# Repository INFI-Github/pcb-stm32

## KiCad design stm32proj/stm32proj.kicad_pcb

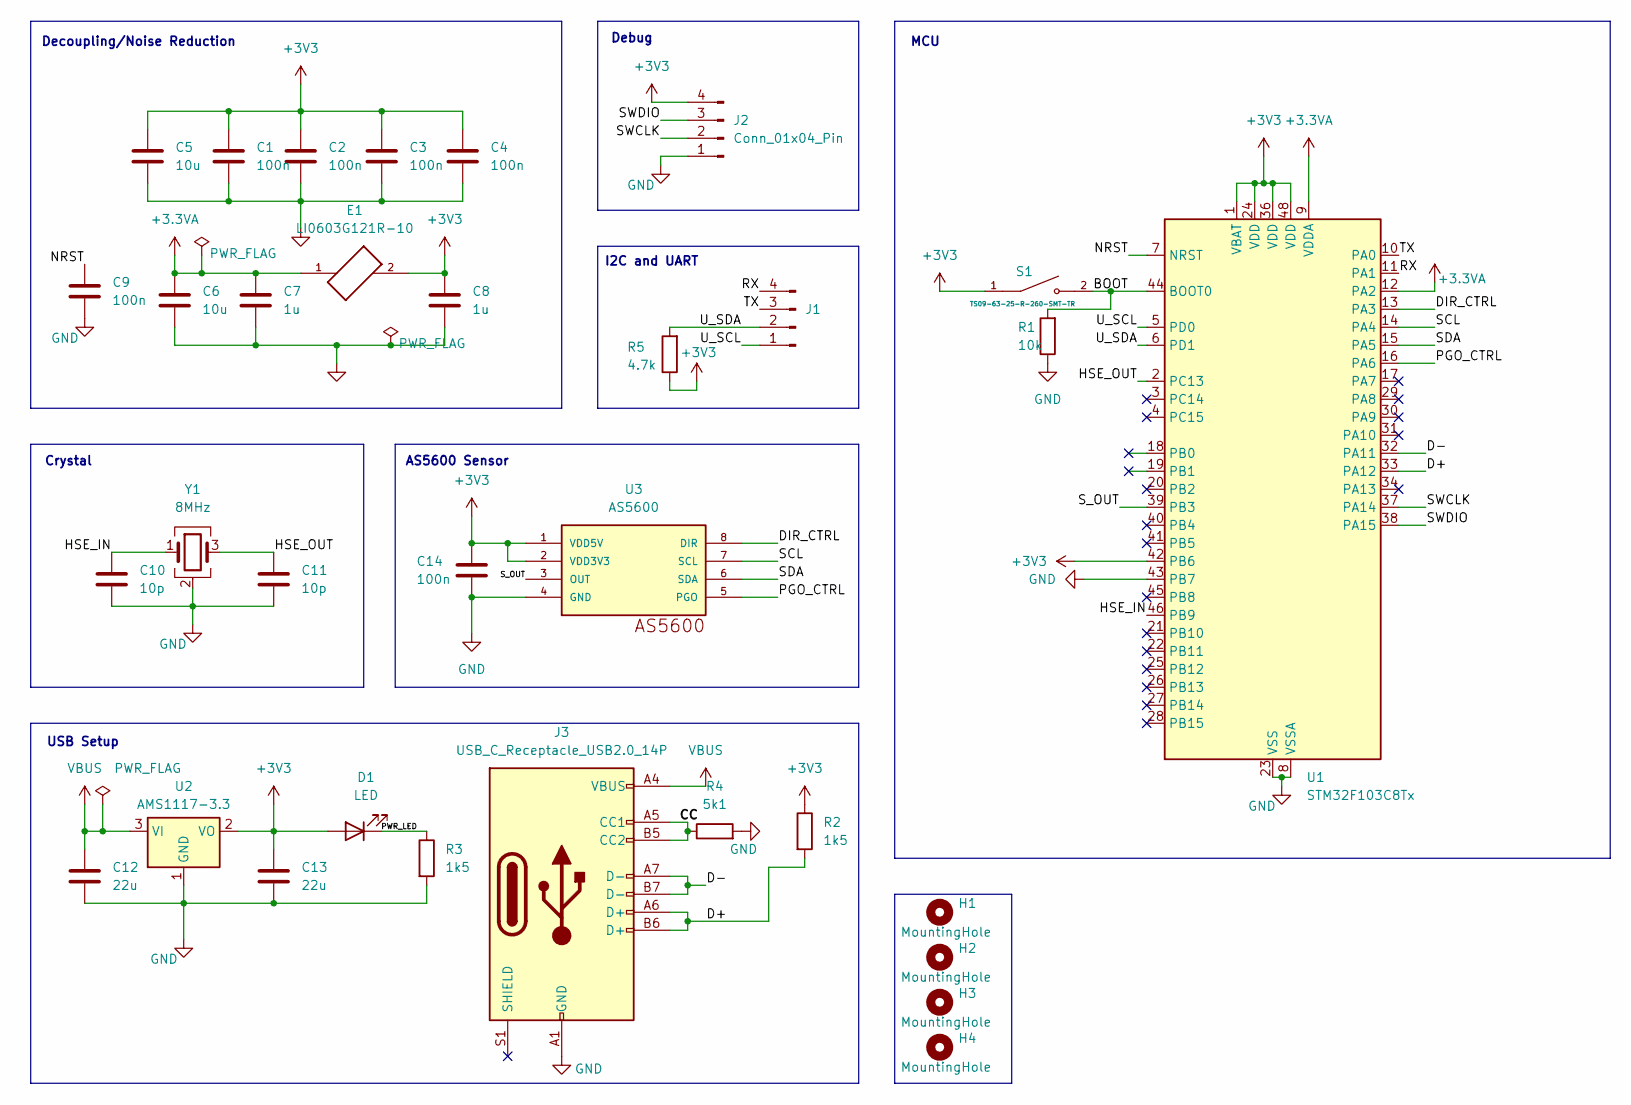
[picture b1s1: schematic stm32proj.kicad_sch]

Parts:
C1, C2, C3, C4, C9, C14: 100n; C_0402_1005Metric
C5, C6: 10u; C_0402_1005Metric
C7, C8: 1u; C_0402_1005Metric
C10, C11: 10p; C_0402_1005Metric
C12, C13: 22u; C_0805_2012Metric
D1: LED; LED_01005_0402Metric
E1: LI0603G121R-10; FB_LI0603G121R-10; PARTREV C
H1, H2, H3, H4: MountingHole; MountingHole_2.1mm
J1, J2: Conn_01x04_Pin; PinHeader_1x04_P1.00mm_Vertical
J3: USB_C_Receptacle_USB2.0_14P; USB_C_Receptacle_GCT_USB4105-xx-A_16P_TopMnt_Horizontal
R1: 10k; R_0402_1005Metric
R2, R3: 1k5; R_0402_1005Metric
R4: 5k1; R_0402_1005Metric
R5: 4.7k; R_0402_1005Metric
S1: TS09-63-25-R-260-SMT-TR; SW_TS09-63-25-R-260-SMT-TR; PARTREV 1.0
U1: STM32F103C8Tx; LQFP-48_7x7mm_P0.5mm
U2: AMS1117-3.3; SOT-223-3_TabPin2
U3: AS5600; SOIC8
Y1: 8MHz; Crystal_SMD_3225-4Pin_3.2x2.5mm

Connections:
+3.3VA: C6.1, C7.1, E1.1, U1.9 (VDDA), U1.12 (PA2)
+3V3: C1.1, C2.1, C3.1, C4.1, C5.1, C8.1, C13.1, C14.1, D1.2 (A), E1.2, J2.4, R2.1, R5.1, S1.1, U1.1 (VBAT), U1.24 (VDD), U1.36 (VDD), U1.42 (PB6), U1.48 (VDD), U2.2 (VO), U3.1 (VDD5V), U3.2 (VDD3V3)
/BOOT: R1.2, S1.2, U1.44 (BOOT0)
/CC: J3.A5 (CC1), J3.B5 (CC2), R4.1
/D+: J3.A6 (D+), J3.B6 (D+), R2.2, U1.33 (PA12)
/D-: J3.A7 (D-), J3.B7 (D-), U1.32 (PA11)
/DIR_CTRL: U1.13 (PA3), U3.8 (DIR)
/HSE_IN: C10.1, U1.46 (PB9), Y1.1
/HSE_OUT: C11.1, U1.2 (PC13), Y1.3
/NRST: C9.1, U1.7 (NRST)
/PGO_CTRL: U1.16 (PA6), U3.5 (PGO)
/PWR_LED: D1.1 (K), R3.1
/RX: J1.4, U1.11 (PA1)
/SCL: U1.14 (PA4), U3.7 (SCL)
/SDA: U1.15 (PA5), U3.6 (SDA)
/SWCLK: J2.2, U1.37 (PA14)
/SWDIO: J2.3, U1.38 (PA15)
/S_OUT: U1.39 (PB3), U3.3 (OUT)
/TX: J1.3, U1.10 (PA0)
/U_SCL: J1.1, U1.5 (PD0)
/U_SDA: J1.2, R5.2, U1.6 (PD1)
GND: C1.2, C2.2, C3.2, C4.2, C5.2, C6.2, C7.2, C8.2, C9.2, C10.2, C11.2, C12.2, C13.2, C14.2, J2.1, J3.A1 (GND), J3.A12 (GND), J3.B1 (GND), J3.B12 (GND), R1.1, R3.2, R4.2, U1.8 (VSSA), U1.23 (VSS), U1.35 (VSS), U1.43 (PB7), U1.47 (VSS), U2.1 (GND), U3.4 (GND), Y1.2 (G), Y1.4 (G)
VBUS: C12.1, J3.A4 (VBUS), J3.A9 (VBUS), J3.B4 (VBUS), J3.B9 (VBUS), U2.3 (VI)

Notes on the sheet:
Decoupling/Noise Reduction
USB Setup
AS5600 Sensor
I2C and UART
Debug
MCU
Crystal

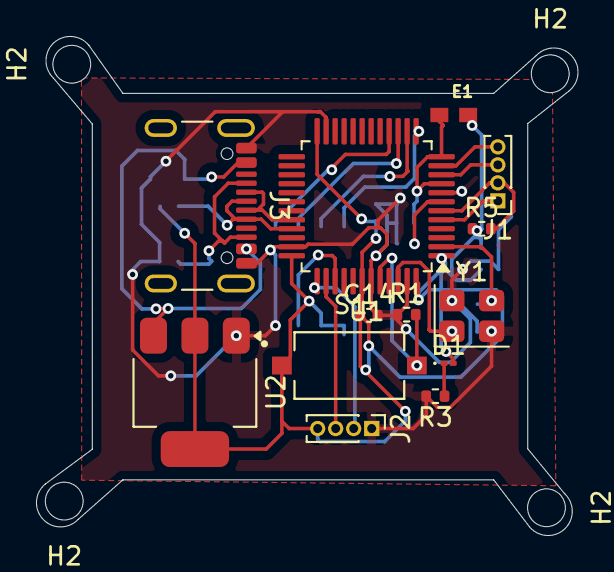
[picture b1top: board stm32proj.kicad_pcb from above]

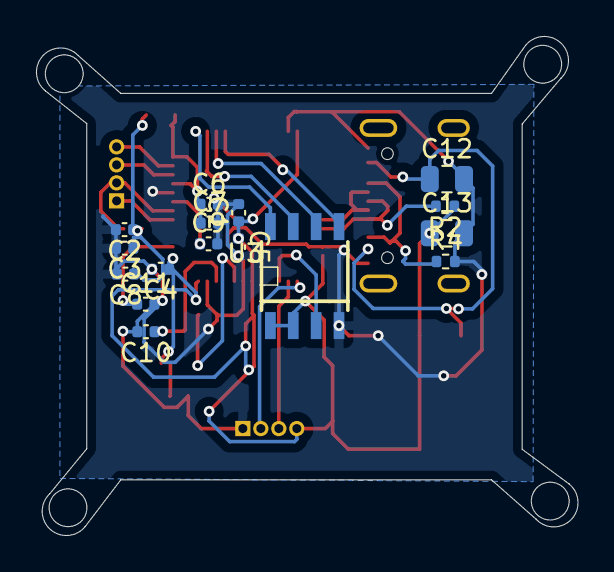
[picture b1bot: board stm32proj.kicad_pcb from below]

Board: 2 copper layers, 30.1 x 27.7 mm, 33 parts (16 on the bottom side), 23 nets.

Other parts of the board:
H2#2, H2#3, H2#4: MountingHole; MountingHole_2.1mm

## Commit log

2026-02-15 schematics done
2026-02-18 connection errors resolved
2026-02-19 added mounting holes
